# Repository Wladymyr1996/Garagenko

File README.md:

# Garagenko
Garagenko is a project of remote controller for garage door or gate.<br><br>
You can set youre language in Garagenko.ino, in define option LANG. You must wite code of youre language.<br>
Now you can set next languages:<br>
* Ukrainian     0
* English       1
* Russian       2

Ви можете встановити Вашу мову у файлі Garagenko.ino в LANG встановіть код Вашої мови.<br>
Наразі доступні коди:<br>
* Українська    0
* Англійська    1
* Російська     2

Вы можете использовать Ваш язык в файле Garagenko.ino в LANG утсановите код Вашего языка.<br>
Сейчас доступны коды:
* Украинский    0
* Английский    1
* Русский       2

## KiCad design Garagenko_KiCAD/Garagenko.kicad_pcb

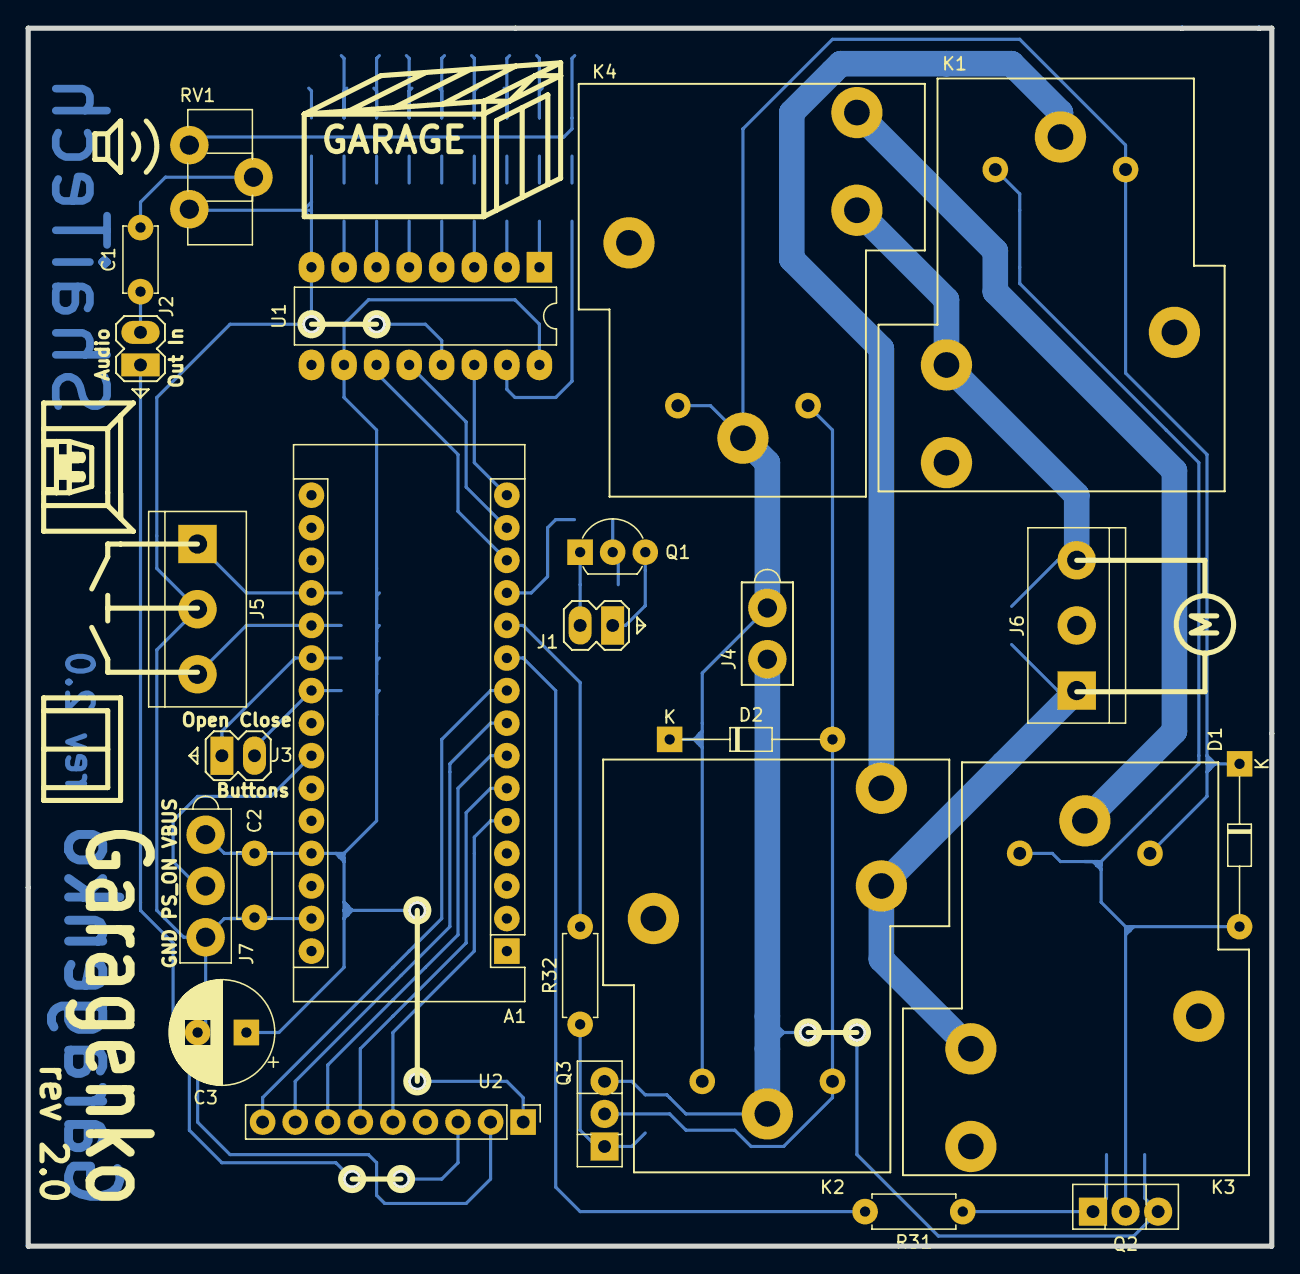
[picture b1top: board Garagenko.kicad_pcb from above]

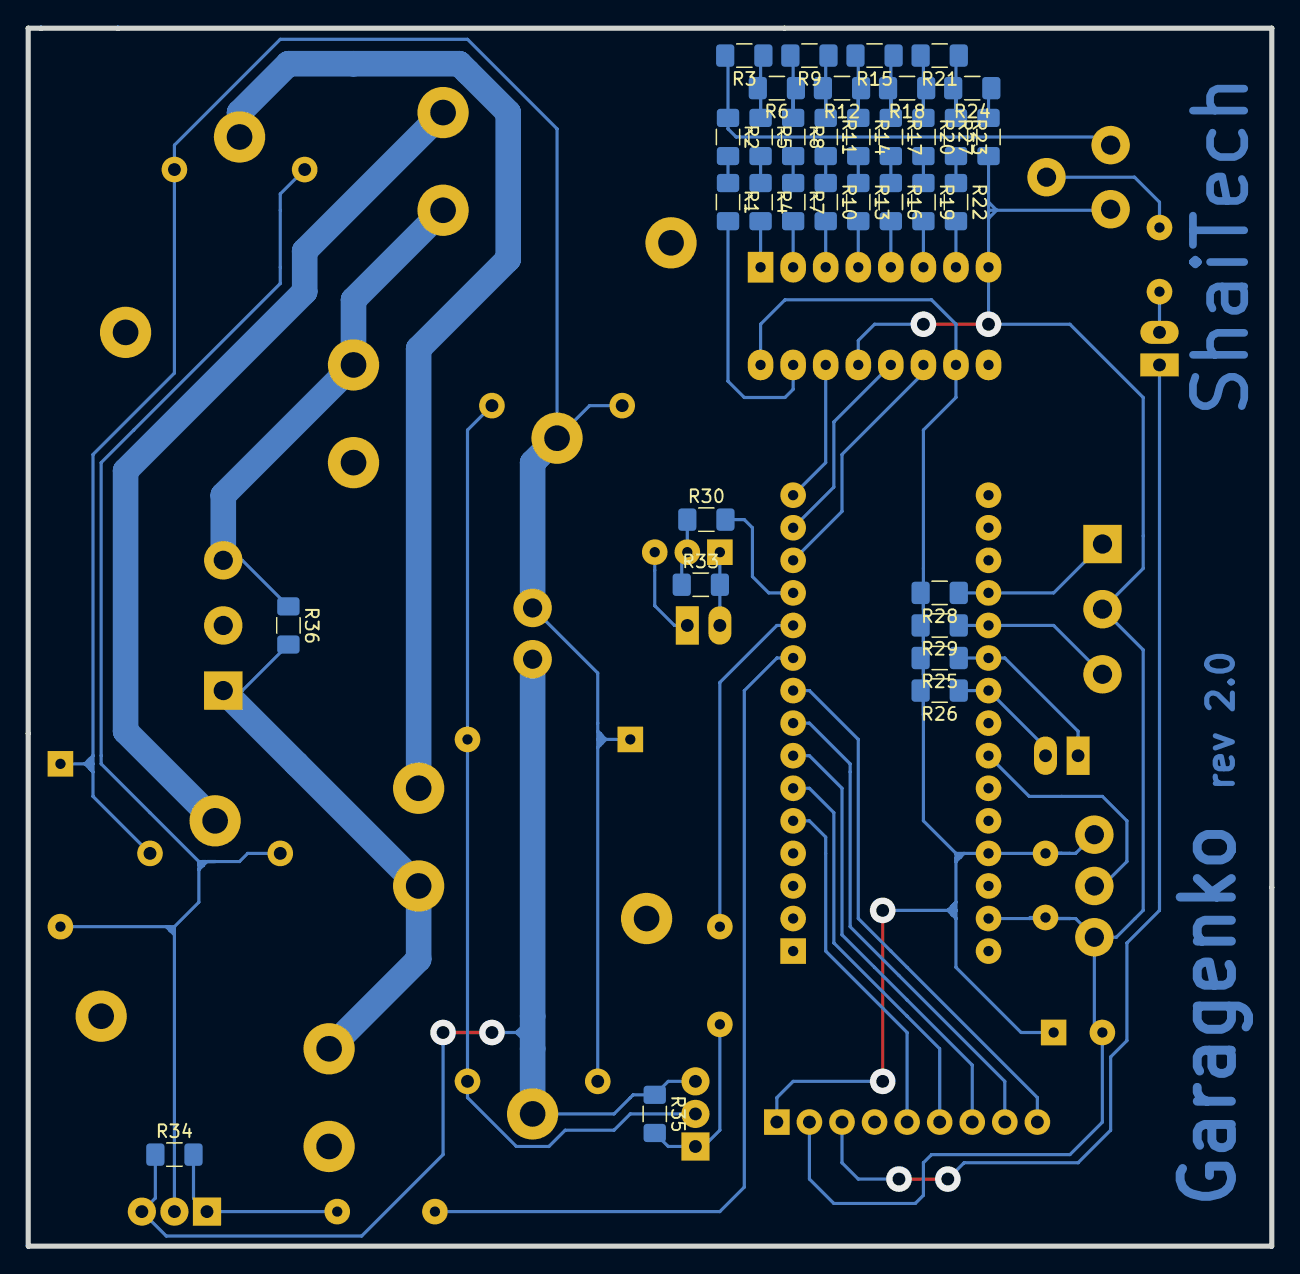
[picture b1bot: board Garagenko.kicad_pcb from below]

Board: 2 copper layers, 97.0 x 95.0 mm, 59 parts (34 on the bottom side), 59 nets.

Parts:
A1: Arduino_Nano_v3.x; Arduino_Nano
C1, C2: 100nF; C_Disc_D5.0mm_W2.5mm_P5.00mm
C3: 1000uF; CP_Radial_D8.0mm_P3.80mm
D1, D2: 1N4007; D_DO-34_SOD68_P12.70mm_Horizontal
J1: btnCallEnd; Conn_1x2_d1mm
J2: audio; Conn_1x2_d1mm
J3: Buttons; Conn_1x2_d1mm
J4: POWER; Conn_1x2_d1.5mm
J5: Limit Switches; TerminalBlock_bornier-3_P5.08mm
J6: Motor Out; TerminalBlock_bornier-3_P5.08mm
J7: ATX; Conn_1x3_d1.5mm
K1, K2, K3, K4: JQX-15F
Q1: BC547; TO-92L_Inline_Wide
Q2, Q3: BD137; TO-126-3_Vertical
R1, R2, R3, R4, R5, R6, R7, R8, R9, R10, R11, R12, R13, R14, R15, R16, R17, R18, R19, R20, R21, R22, R23, R24, R27, R30, R33, R34, R35, R36: 2.2K; R_1206_3216Metric_Pad1.42x1.75mm_HandSolder
R25, R26, R28, R29: 4.7K; R_1206_3216Metric_Pad1.42x1.75mm_HandSolder
R31, R32: 220R; R_Axial_DIN0207_L6.3mm_D2.5mm_P7.62mm_Horizontal
RV1: 20k; Potentiometer_Piher_PT-10-H05_Horizontal
U1: 74HC595; DIP-16_W7.62mm_LongPads
U2: MT8870_Module; PinHeader_1x09_P2.54mm_Vertical

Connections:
+12V: D1.1, D2.1, J4.1, K1.2, K2.2, K3.2, K4.2, K4.3
AudioOut: C1.1, J2.2
Btn_Close: A1.22, J3.2, R26.1
Btn_Open: A1.21, J3.1, R25.1
DS: A1.15, U1.14
GND: J4.2, K2.3, Q2.3, Q3.3, R34.1, R35.1
GNDD: A1.29, C2.2, C3.2, J5.2, J7.3, R27.1, RV1.3, U1.8, U1.13, U2.2
Limit_Swch_Close: A1.20, J5.3, R29.1
Limit_Swch_Open: A1.19, J5.1, R28.1
M1: J6.1, K2.5, K3.5
M2: J6.3, K1.5, K4.5
M_Close: A1.11, R32.2
M_Open: A1.10, R31.2
unnamed: C1.2, RV1.2
unnamed: D1.2, K1.4, K3.4, Q2.2
unnamed: D2.2, K2.4, K4.4, Q3.2
unnamed: K1.3, K2.6
unnamed: K3.3, K4.6
unnamed: Q1.2, R30.1, R33.1
unnamed: Q2.1, R31.1, R34.2
unnamed: Q3.1, R32.1, R35.2
unnamed: R1.1, R2.2
unnamed: R1.2, U1.15
unnamed: R2.1, R3.2, RV1.1
unnamed: R3.1, R5.1, R6.2
unnamed: R4.1, R5.2
unnamed: R4.2, U1.1
unnamed: R6.1, R8.1, R9.2
unnamed: R7.1, R8.2
unnamed: R7.2, U1.2
unnamed: R10.1, R11.2
unnamed: R10.2, U1.3
unnamed: R9.1, R11.1, R12.2
unnamed: R12.1, R14.1, R15.2
unnamed: R13.1, R14.2
unnamed: R13.2, U1.4
unnamed: R15.1, R17.1, R18.2
unnamed: R16.1, R17.2
unnamed: R16.2, U1.5
unnamed: R18.1, R20.1, R21.2
unnamed: R19.1, R20.2
unnamed: R19.2, U1.6
unnamed: R21.1, R23.1, R24.2
unnamed: R22.1, R23.2
unnamed: R22.2, U1.7
unnamed: R24.1, R27.2
PS_ON: A1.24, J7.2
PhoneAudio: J2.1, U2.3
Q1: A1.9, U2.9
Q2: A1.8, U2.8
Q3: A1.7, U2.7
Q4: A1.6, U2.6
SH_CP: A1.13, U1.11
ST_CP: A1.14, U1.12
StQ: A1.5, U2.5
VBUS: A1.27, C2.1, C3.1, J7.1, R25.2, R26.2, R28.2, R29.2, U1.10, U1.16, U2.1
btnCallEnd: A1.12, R30.2
btnCallEndIn: J1.1, Q1.3
btnCallEndOut: J1.2, Q1.1, R33.2

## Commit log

2018-10-04 Adding project files
2018-10-05 Adding License file
2018-10-05 Adding files
2018-10-05 repair
